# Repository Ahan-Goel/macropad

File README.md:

# macropad
Created a Macropad utilizing an embedded processor and QMK to program it

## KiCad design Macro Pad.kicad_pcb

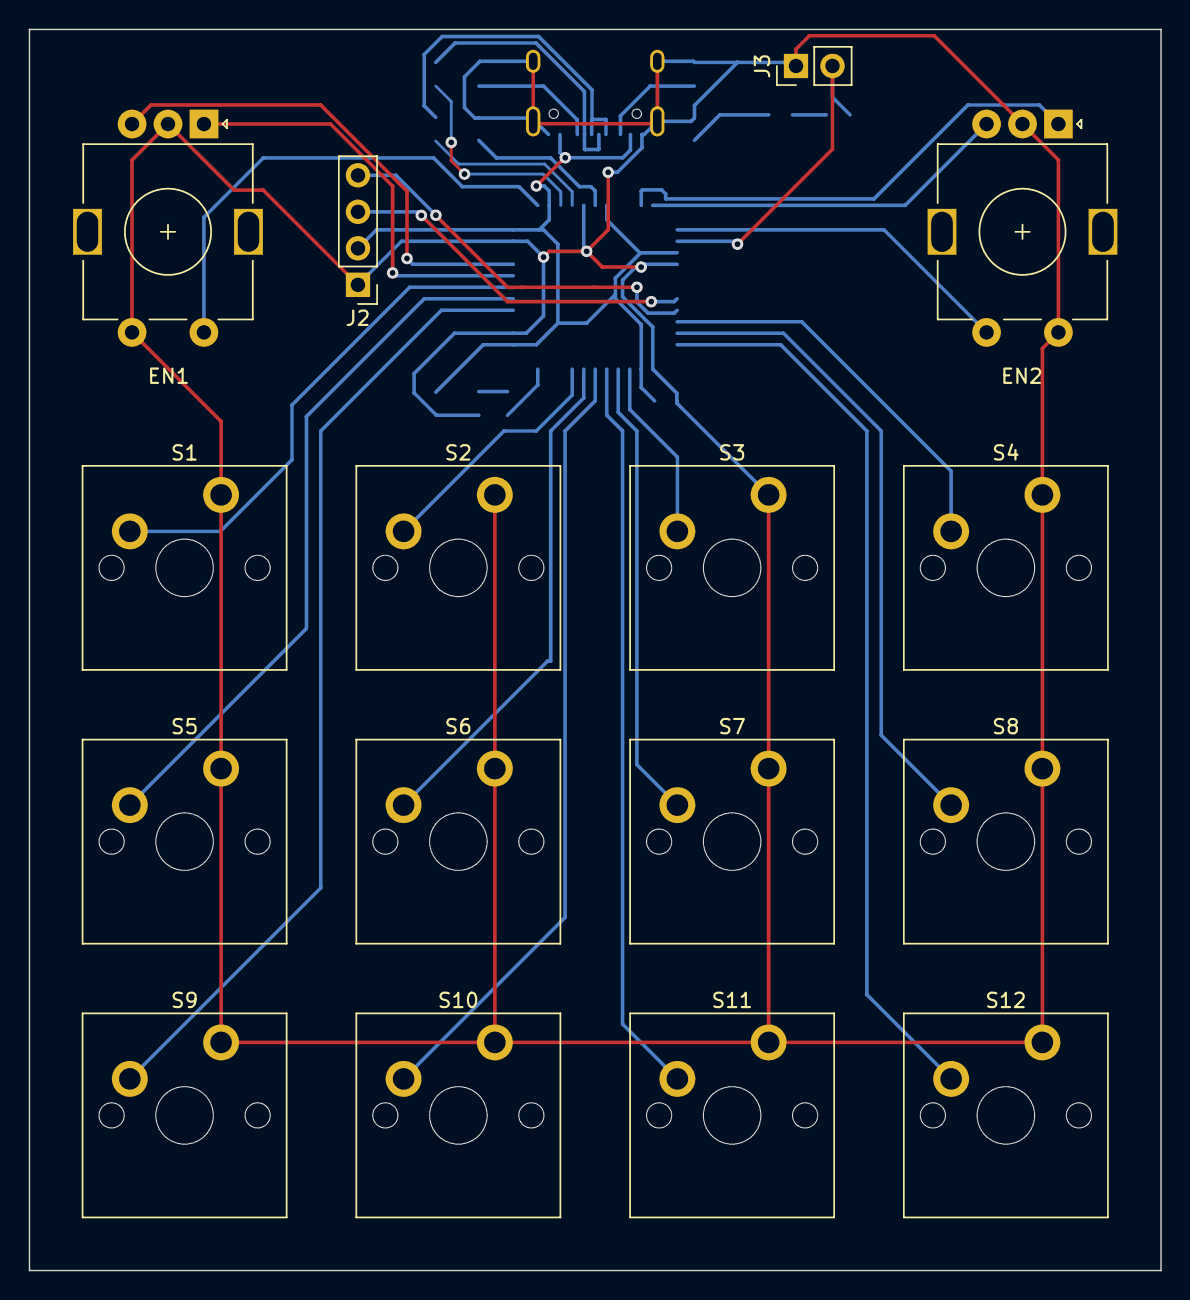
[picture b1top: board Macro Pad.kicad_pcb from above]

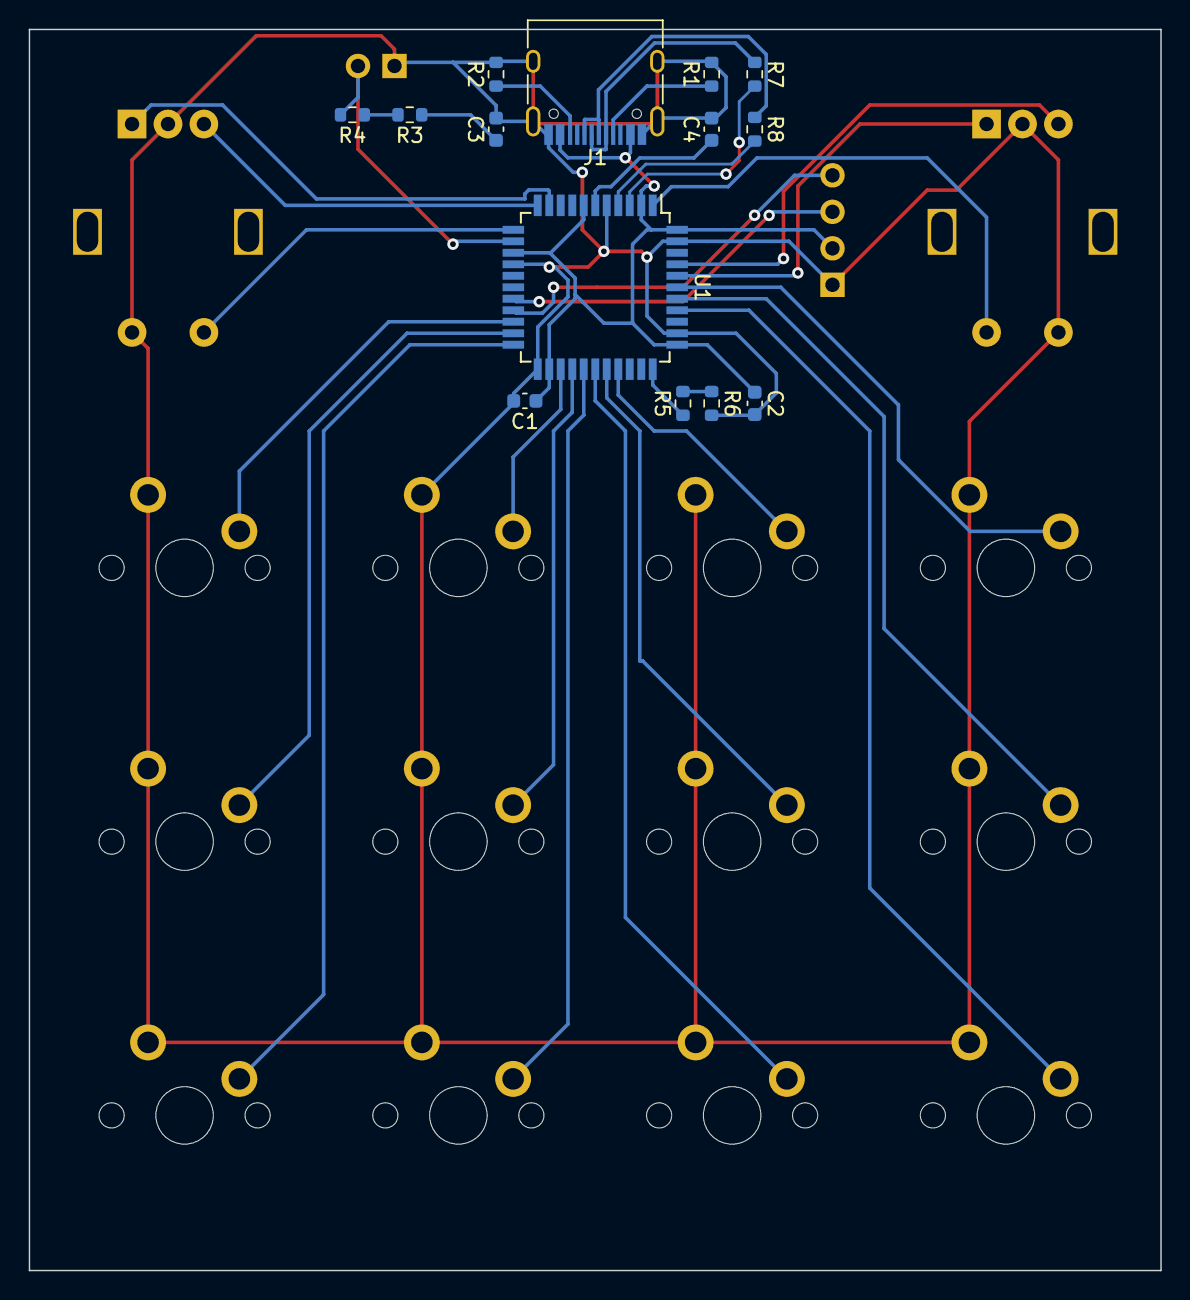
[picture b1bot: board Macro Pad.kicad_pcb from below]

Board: 2 copper layers, 78.7 x 86.4 mm, 30 parts (14 on the bottom side), 33 nets.

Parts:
C1, C2: 100nF; C_0603_1608Metric
C3: 4.7uF; C_0603_1608Metric
C4: 1uF; C_0603_1608Metric
EN1, EN2: RotaryEncoder_Switch; RotaryEncoder_Alps_EC11E-Switch_Vertical_H20mm
J1: USB_C_Receptacle_USB2.0; USB_C_Receptacle_HRO_TYPE-C-31-M-12
J2: OLED; PinHeader_1x04_P2.54mm_Vertical
J3: Reset; PinHeader_1x02_P2.54mm_Vertical
R1, R2, R3, R4, R5, R6: 5.1k; R_0603_1608Metric
R7, R8: 22; R_0603_1608Metric
S1, S2, S3, S4, S5, S6, S7, S8, S9, S10, S11, S12: Keyswitch; MX_PCB_1.00u
U1: ATMEGA32U4-AUR; TQFP-44_10x10mm_P0.8mm

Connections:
+5V: C1.1, C2.1, C3.1, J1.A4 (VBUS), J1.A9 (VBUS), J1.B4 (VBUS), J1.B9 (VBUS), J2.2, R3.1, U1.2 (UVCC), U1.7 (VBUS), U1.14 (VCC), U1.24 (AVCC), U1.34 (VCC), U1.44 (AVCC)
D+: R8.2, U1.4 (D+)
D-: R7.2, U1.3 (D-)
GND: C1.2, C2.2, C3.2, C4.2, EN1.C, EN1.S1, EN2.C, EN2.S2, J1.A1 (GND), J1.A12 (GND), J1.B1 (GND), J1.B12 (GND), J1.S1 (SHIELD), J2.1, J3.1, R1.2, R2.2, R6.2, S1.2, S2.2, S3.2, S4.2, S5.2, S6.2, S7.2, S8.2, S9.2, S10.2, S11.2, S12.2, U1.5 (UGND), U1.15 (GND), U1.23 (GND), U1.35 (GND), U1.43 (GND)
unnamed: J1.A5 (CC1), R1.1
unnamed: J1.B5 (CC2), R2.1
unnamed: J1.A6 (D+), J1.B6 (D+), R8.1
unnamed: J1.A7 (D-), J1.B7 (D-), R7.1
unnamed: R3.2, R4.1
unnamed: R5.2, R6.1
unnamed: C4.1, U1.6 (UCAP)
unnamed: R5.1, U1.33 (~HWB/PE2)
Reset: J3.2, R4.2, U1.13 (~RESET)
Rotary 1 A: EN1.A, U1.40 (PF1)
Rotary 1 B: EN1.B, U1.41 (PF0)
Rotary 2 A: EN2.B, U1.11 (PB3)
Rotary 2 B: EN2.A, U1.10 (PB2)
S1: S1.1, U1.39 (PF4)
S2: S2.1, U1.30 (PB6)
S3: S3.1, U1.25 (PD4)
S4: S4.1, U1.20 (PD2)
S5: S5.1, U1.38 (PF5)
S6: S6.1, U1.29 (PB5)
S7: S7.1, U1.26 (PD6)
S8: S8.1, U1.21 (PD3)
S9: S9.1, U1.37 (PF6)
S10: S10.1, U1.28 (PB4)
S11: S11.1, U1.27 (PD7)
S12: S12.1, U1.22 (PD5)
S13: EN1.S2, U1.1 (PE6)
S14: EN2.S1, U1.12 (PB7)
SCL: J2.3, U1.18 (PD0)
SDA: J2.4, U1.19 (PD1)

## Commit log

2023-12-08 Adding preliminary design
2023-12-08 Adding preliminary schematic
2023-12-09 Added two rotary encoders
2024-01-07 Adding Files
2024-04-12 Test
2024-04-12 Edited Readme
2024-05-20 Adding project file
2024-08-23 Adding License
2024-09-09 Adding changes
